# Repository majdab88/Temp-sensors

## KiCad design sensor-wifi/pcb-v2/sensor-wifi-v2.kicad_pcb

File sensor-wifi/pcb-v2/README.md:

# sensor-wifi PCB v2 — TP4056 module instead of the on-board charger

Same board as v1 (`../pcb`), with the USB-C receptacle, the BQ24074 charger and
the DW01A/8205A cell protection replaced by a **TP4056 Mini Type-C charger
module** (14 × 17.5 mm, with its own protection) soldered flat onto the PCB.
The point is cost: JLCPCB's Extended parts drop from 11 to **4**. The v1 design
is kept unchanged in `../pcb`.

**Status:** placed and routed. ERC clean; DRC 0 errors, 0 unconnected,
schematic parity clean. The 45 warnings are silkscreen overlaps. Not built.

## What changed from v1

| | v1 | v2 |
|---|---|---|
| USB input | J1 USB-C, F1 PTC, D1 TVS, CC and shield parts | the module's own USB-C (J1's place, same enclosure wall) |
| Charging | BQ24074, 0.5 A, power path, TS thermistor | module's TP4056 (4056H), **~0.6 A** (its R_PROG is 2 kΩ) |
| Cell protection | DW01A + 8205A + F2 3 A fuse | module's single-chip protector |
| Reverse cell | Q1 (P-FET, + side), DW01A fed through D2 | **Q1 + Q2** (N-FET, − side), see below |
| USB present | BQ24074 `/PGOOD` → GPIO7, active **low** | **100 k / 100 k from module IN+ → GPIO7, active high** |
| Charging status | `/CHG` → GPIO18 | none (GPIO18 unused) |
| Everything else | | unchanged and at v1's positions: module, TPS63802 loop, NTC, buttons, J_PROG, crystal, holder |

**Firmware:** `USB_DET` (GPIO7) is HIGH when USB is present, the opposite of
`/PGOOD`; GPIO7 is still an LP GPIO, so it still wakes from deep sleep. Drop the
`/CHG` reading. The battery divider (GPIO2/GPIO21) is unchanged and now sits on
VSYS, which is the cell through Q1 (≈ 4.2 V while USB charges).

## The module

`TP4056_Mini_TypeC` footprint and symbol come from `routing/mkfp_tp4056.py`,
measured from the vendor STEP (`3d/TP4056_Mini.step`, GrabCAD, **not committed**:
its licence does not allow redistribution). Six plated holes, 1.0 mm:

| Pad | Name | Net | Position on the board |
|---|---|---|---|
| 1 | IN+ | `VBUS_IN` (divider only) | 101.85, 186.5 |
| 2 | IN− | GND | 114.15, 186.5 |
| 3 | OUT− | GND | 114.15, 172.5 |
| 4 | B− | `BATN` (Q2 source) | 111.61, 172.5 |
| 5 | (unlabelled) | **isolated**, mechanical only | 104.39, 172.5 |
| 6 | + | `VSYS` | 101.85, 172.5 |

- **Solder it** with cut-down pin-header pins through both boards, or let solder
  fill its holes onto our pads. The 18650 holder is on the back but clear of
  the module, so the joints are reachable from below.
- **Pad 5 is not connected** until a continuity check confirms it is a second
  "+" (it probably is). Beep pad 5 to pad 6 on a real module.
- **Check IN− to OUT− continuity**: the USB-detect divider assumes they are the
  same node (they are on standard TP4056 boards).
- **CC resistors**: look for two 5.1 kΩ (512) resistors by the module's USB-C.
  Without them it charges only from USB-A-to-C cables, not C-to-C.
- **No power path**: the ESP draws from the cell node the TP4056 charges. Once the
  cell is full it terminates, the load draws it down to ~4.05 V, and it tops up:
  shallow cycles near full, accepted for this load.
- **No cold-charge cutoff**: the module grounds the TP4056's TEMP pin.
- **Enclosure**: the module's receptacle face is where J1's was (board edge
  + 1.05 mm), but its centre is ~2.6 mm above our board (it sits on the module's
  own PCB), about 1 mm higher than J1's. Move the enclosure's USB opening up to
  match before printing.

## Reverse-cell protection (Q1 + Q2)

With the module, a P-FET on the + side alone (v1's Q1) is not enough. The module's
protector sits between B− and ground and is powered from the charger, so with a
reversed cell **and** USB present Q1 would turn on and the charger would drive
current through the reversed cell. v2 adds an N-FET on the − side:

- **Q1** (AO3401A, P): drain = holder +, source = VSYS, gate via R10 (10 k) to
  holder −, R11 (1 M) to source.
- **Q2** (AO3400A, N, Basic C20917): drain = holder −, source = module B−
  (`BATN`), gate via R12 (10 k) to holder +, R13 (1 M) to source.

| Cell | USB | Q1 | Q2 | Result |
|---|---|---|---|---|
| correct | no / yes | on | on | normal; charge and discharge both ways through both |
| reversed | no | off | off | no path |
| reversed | yes | off | off | each would need the other already on to turn on; no current |

The reversed rows are reasoned, not measured. **Bench-test them** (reversed cell
on a current-limited supply, with and without USB: zero current, no heating)
before trusting the board. This is a safety path.

## JLCPCB parts

21 part numbers: **15 Basic, 2 Preferred, 4 Extended** (U1 ESP32-C6-MINI-1U-H4,
U4 TPS63802, L1 inductor, F3 probe-line PTC). Every SMD part carries `LCSC`, `MPN`
and `Manufacturer`. Hand-soldered: the TP4056 module, BT1 holder (back side),
J2, J3, SW1, SW2.

## Layout

- v1's outline (64 × 90 mm), M3 holes and every kept part at v1's coordinates.
- **Module** where J1 was: centre (108, 180.4), rotated 180°, USB-C out of the
  bottom edge.
- **Q2, R12, R13** beside the holder's − contact (top right), where the DW01A and
  8205A were. **C4/C5** (10 µF) beside the module's + pad. **R8/R9** (USB detect)
  left of the module.
- **Hand-routed** (`routing/handroutes.py`): v1's TPS63802 loop, UART lanes and
  GND ties unchanged; the cell paths (holder + → Q1; holder − → Q2 on 0.8 mm;
  Q2 → module B− on 1 mm down the back); the VSYS trunk from the module's + pad to
  the regulator, Q1 and the battery divider (v1's pinned path for the last part);
  all of EN (Freerouting left a link open); and a back-side tie for C16's ground
  via. Freerouting routed the rest.
- The holder's three plastic pegs go through the board at (131, 172.6),
  (147, 117.4) and (147, 181.1); the VSYS trunk passes the first with 0.8 mm.

## Reproducing it

Same tooling as sensor-ntc v3. Under KiCad's bundled Python:

1. `routing/mkfp_tp4056.py` (any Python) writes the module footprint and symbol.
2. `routing/mkboard.py` builds the unrouted board from the schematic's netlist
   and the placement table.
3. `routing/build.py auto` hand-routes, autoroutes, pours, stitches and runs
   DRC on a copy in `routing/work/`. Good when it reports 0 unconnected; adopt by
   copying `routing/work/sensor-wifi-v2.kicad_pcb` over the project file with
   KiCad closed. `routing/drc-baseline.json` is the adopted board's DRC.

## Before fab

- Continuity checks on a real module: pad 5 ↔ pad 6, IN− ↔ OUT−; CC resistors.
- Move the enclosure's USB opening up ~1 mm for the module's receptacle.
- Tidy the silkscreen; mark pin 1 on J_PROG.
- Bench-test the reverse-cell rows after assembly.

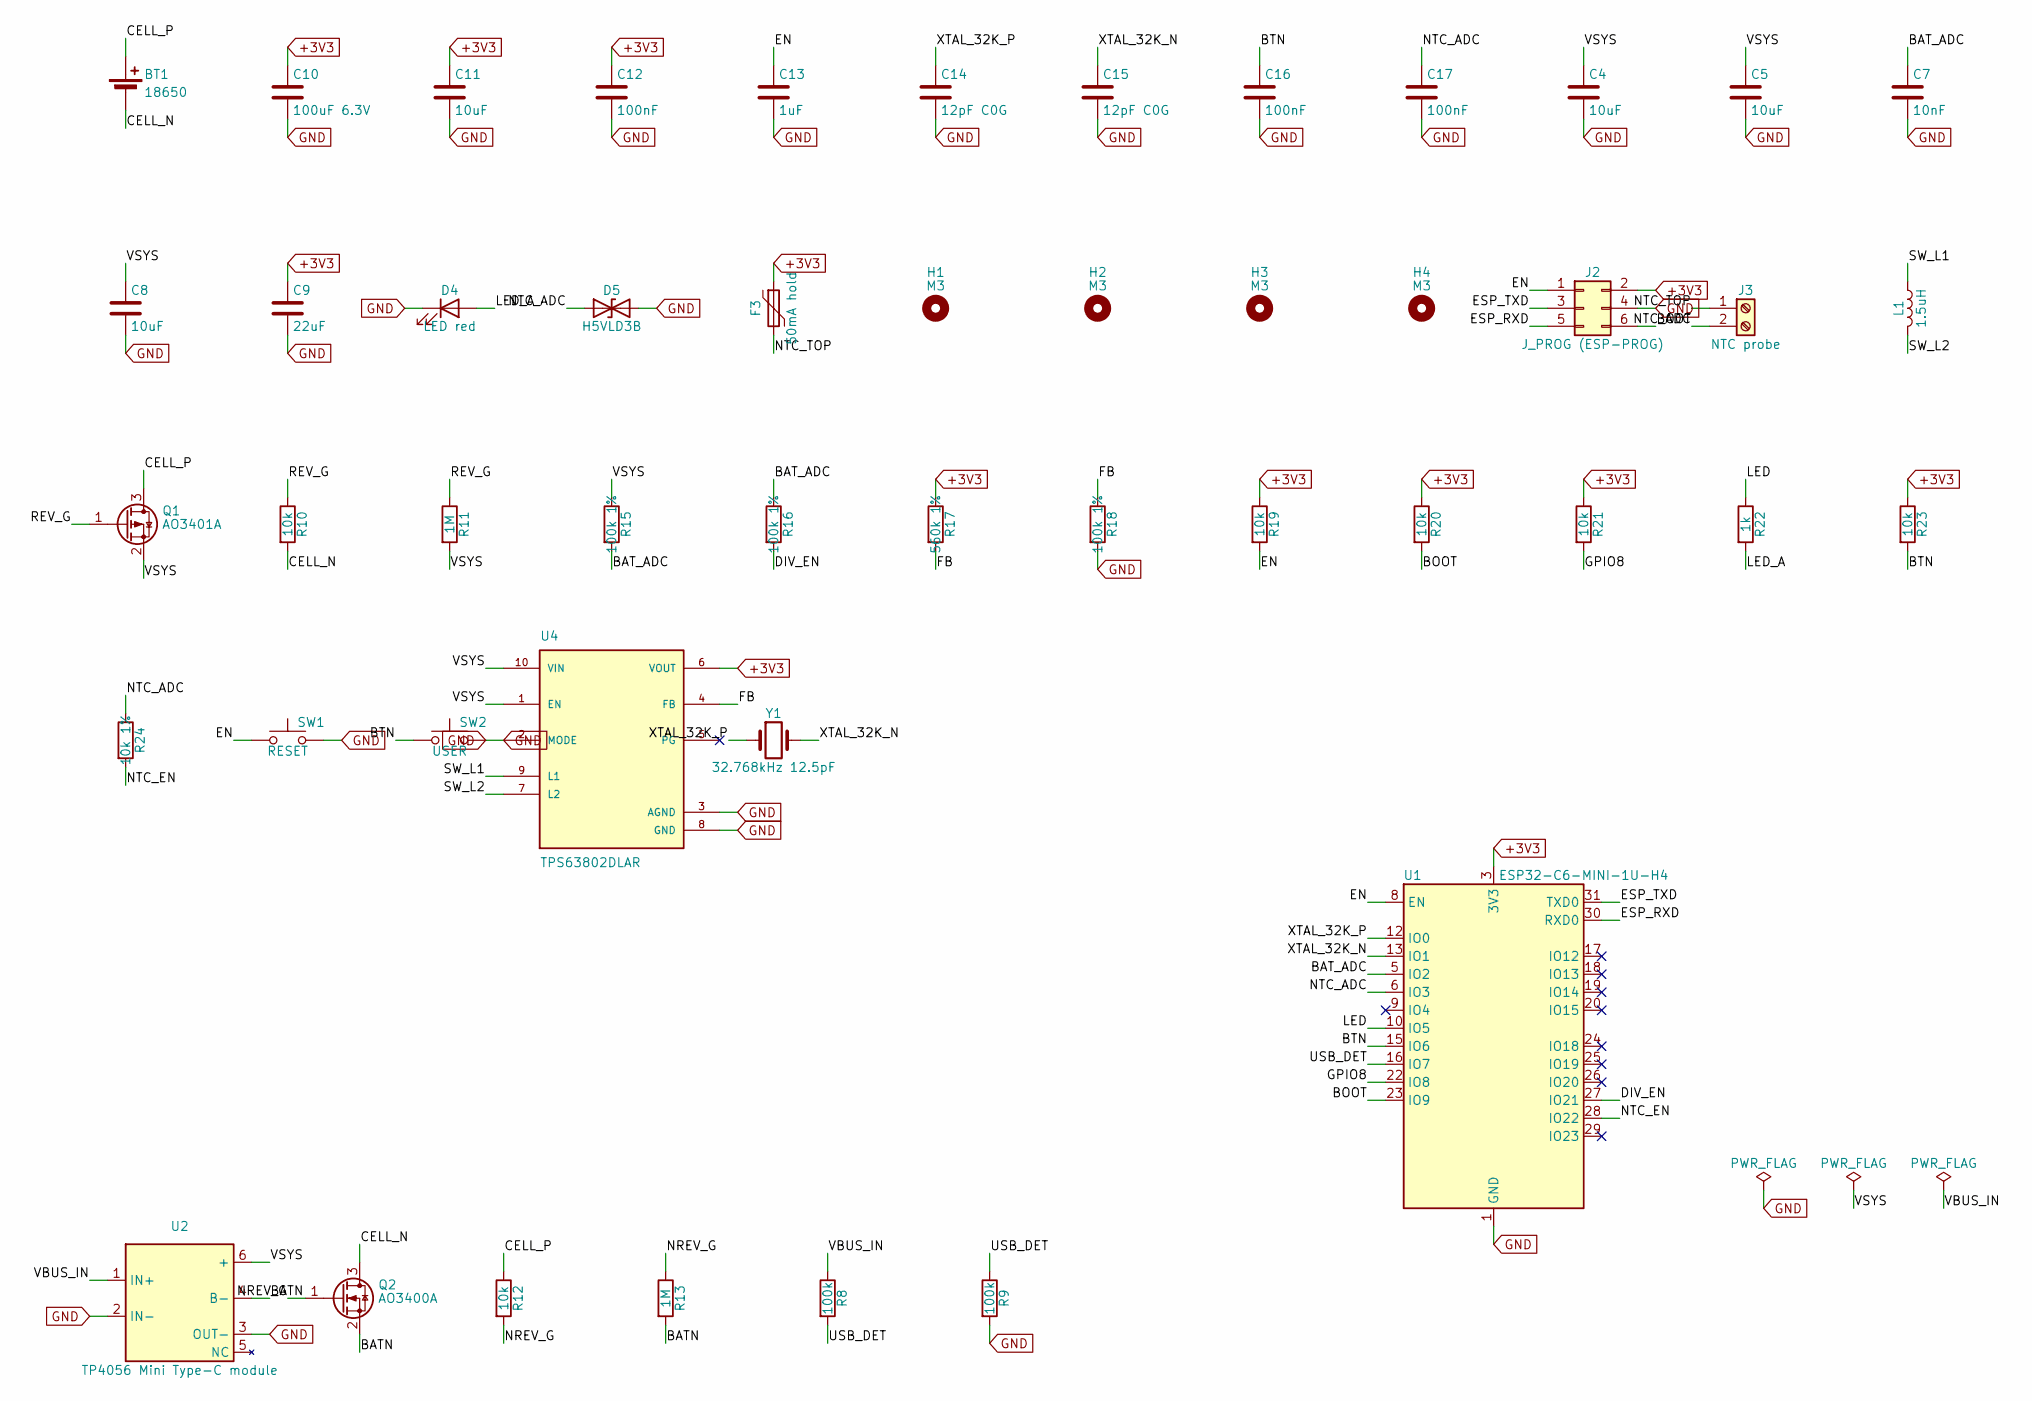
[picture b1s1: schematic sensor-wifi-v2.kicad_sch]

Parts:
BT1: 18650; BatteryHolder_Keystone_1042_1x18650
C4, C5, C8, C11: 10uF; C_0805_2012Metric; MPN CL21A106KAYNNNE; LCSC C15850
C7: 10nF; C_0603_1608Metric; MPN 0603B103K500NT; LCSC C57112
C9: 22uF; C_1206_3216Metric; MPN CL31A226KAHNNNE; LCSC C12891
C10: 100uF 6.3V; C_1206_3216Metric; MPN CL31A107MQHNNNE; LCSC C15008
C12, C16, C17: 100nF; C_0603_1608Metric; MPN CC0603KRX7R9BB104; LCSC C14663
C13: 1uF; C_0603_1608Metric; MPN CL10A105KB8NNNC; LCSC C15849
C14, C15: 12pF C0G; C_0603_1608Metric; MPN CL10C120JB8NNNC; LCSC C38523
D4: LED red; LED_0603_1608Metric; MPN KT-0603R; LCSC C2286
D5: H5VLD3B; D_SOD-323; MPN H5VLD3B; LCSC C20615805
F3: 50mA hold; Fuse_0805_2012Metric; MPN BSMD0805-005-60V; LCSC C960019
H1, H2, H3, H4: M3; MountingHole_3.2mm_M3
J2: J_PROG (ESP-PROG); IDC-Header_2x03_P2.54mm_Vertical
J3: NTC probe; TerminalBlock_Phoenix_PT-1,5-2-3.5-H_1x02_P3.50mm_Horizontal
L1: 1.5uH; VLS3015; MPN FNR3015S1R5MT; LCSC C167745
Q1: AO3401A; SOT-23; MPN AO3401A; LCSC C15127
Q2: AO3400A; SOT-23; MPN AO3400A; LCSC C20917
R8, R9: 100k; R_0603_1608Metric; MPN 0603WAF1003T5E; LCSC C25803
R10, R12, R19, R20, R21, R23: 10k; R_0603_1608Metric; MPN 0603WAF1002T5E; LCSC C25804
R11, R13: 1M; R_0603_1608Metric; MPN 0603WAF1004T5E; LCSC C22935
R15, R16, R18: 100k 1%; R_0603_1608Metric; MPN 0603WAF1003T5E; LCSC C25803
R17: 560k 1%; R_0603_1608Metric; MPN 0603WAF5603T5E; LCSC C23203
R22: 1k; R_0603_1608Metric; MPN 0603WAF1001T5E; LCSC C21190
R24: 10k 1%; R_0603_1608Metric; MPN 0603WAF1002T5E; LCSC C25804
SW1: RESET; SW_PUSH_6mm_H5mm
SW2: USER; SW_PUSH_6mm_H5mm
U1: ESP32-C6-MINI-1U-H4; ESP32-C6-MINI-1U; MPN ESP32-C6-MINI-1U-H4; LCSC C20627095
U2: TP4056 Mini Type-C module; TP4056_Mini_TypeC
U4: TPS63802DLAR; VREG_TPS63802DLAR; PARTREV B; LCSC C2845237
Y1: 32.768kHz 12.5pF; Crystal_SMD_3215-2Pin_3.2x1.5mm; MPN Q13FC13500004; LCSC C32346

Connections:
+3V3: C9.1, C10.1, C11.1, C12.1, F3.1, J2.2, R17.1, R19.1, R20.1, R21.1, R23.1, U1.3 (3V3), U4.6 (VOUT)
/BATN: Q2.2 (S), R13.2, U2.4 (B-)
/BAT_ADC: C7.1, R15.2, R16.1, U1.5 (IO2)
/BOOT: J2.6, R20.2, U1.23 (IO9)
/BTN: C16.1, R23.2, SW2.1, U1.15 (IO6)
/CELL_N: BT1.2 (-), Q2.3 (D), R10.2
/CELL_P: BT1.1 (+), Q1.3 (D), R12.1
/DIV_EN: R16.2, U1.27 (IO21)
/EN: C13.1, J2.1, R19.2, SW1.1, U1.8 (EN)
/ESP_RXD: J2.5, U1.30 (RXD0)
/ESP_TXD: J2.3, U1.31 (TXD0)
/FB: R17.2, R18.1, U4.4 (FB)
/GPIO8: R21.2, U1.22 (IO8)
/LED: R22.1, U1.10 (IO5)
/LED_A: D4.2 (A), R22.2
/NREV_G: Q2.1 (G), R12.2, R13.1
/NTC_ADC: C17.1, D5.1 (A1), J3.2, R24.1, U1.6 (IO3)
/NTC_EN: R24.2, U1.28 (IO22)
/NTC_TOP: F3.2, J3.1
/REV_G: Q1.1 (G), R10.1, R11.1
/SW_L1: L1.1, U4.9 (L1)
/SW_L2: L1.2, U4.7 (L2)
/USB_DET: R8.2, R9.1, U1.16 (IO7)
/VBUS_IN: R8.1, U2.1 (IN+)
/VSYS: C4.1, C5.1, C8.1, Q1.2 (S), R11.2, R15.1, U2.6 (+), U4.1 (EN), U4.10 (VIN)
/XTAL_32K_N: C15.1, U1.13 (IO1), Y1.2
/XTAL_32K_P: C14.1, U1.12 (IO0), Y1.1
GND: C4.2, C5.2, C7.2, C8.2, C9.2, C10.2, C11.2, C12.2, C13.2, C14.2, C15.2, C16.2, C17.2, D4.1 (K), D5.2 (A2), J2.4, R9.2, R18.2, SW1.2, SW2.2, U1.1 (GND), U1.2 (GND), U1.11 (GND), U1.14 (GND), U1.36 (GND), U1.37 (GND), U1.38 (GND), U1.39 (GND), U1.40 (GND), U1.41 (GND), U1.42 (GND), U1.43 (GND), U1.44 (GND), U1.45 (GND), U1.46 (GND), U1.47 (GND), U1.48 (GND), U1.49 (GND), U1.50 (GND), U1.51 (GND), U1.52 (GND), U1.53 (GND), U2.2 (IN-), U2.3 (OUT-), U4.2 (MODE), U4.3 (AGND), U4.8 (GND)

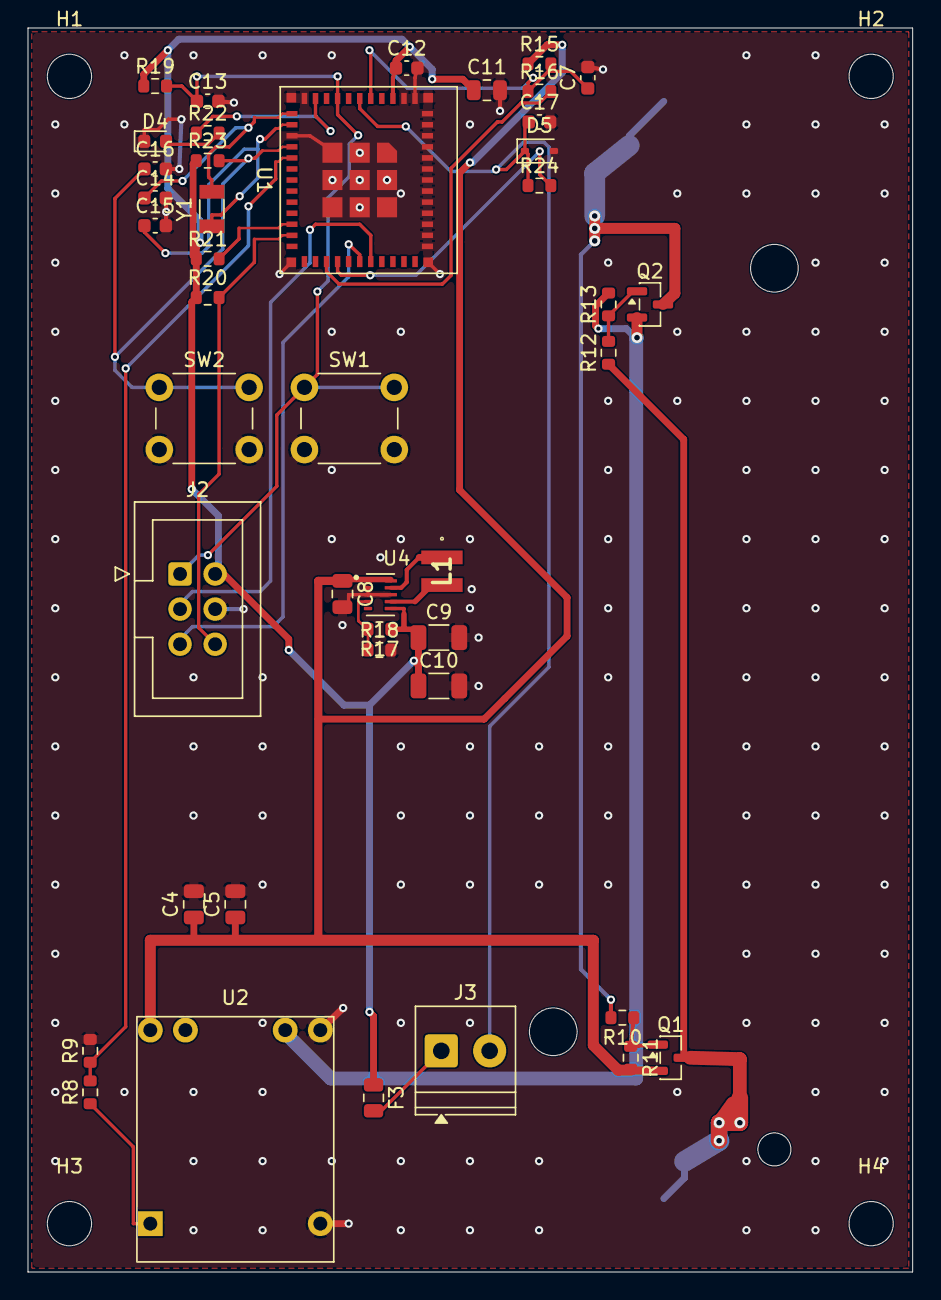
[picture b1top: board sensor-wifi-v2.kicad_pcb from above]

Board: 2 copper layers, 64.0 x 90.0 mm, 48 parts (1 on the bottom side), 28 nets.

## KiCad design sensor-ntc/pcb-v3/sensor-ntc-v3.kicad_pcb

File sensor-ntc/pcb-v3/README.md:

# sensor-ntc v3 PCB

The v2 sensor board, redesigned around the **ESP32-C6-MINI-1U-H4** (the module
sensor-wifi uses), with the NTC back on the **high side** and a connector for the
**12 mm panel button with its LED ring**. KiCad 10 project, 2 layers, 1.6 mm.

Placed and routed. **DRC: 0 errors, 0 unconnected, schematic parity clean.** The
59 remaining findings are silkscreen text overlaps (a GUI tidy job) and two
reference labels near the board edge. Not yet fabricated.

## What changed from v2

| | v2 (NTC_SENSOR) | v3 |
|---|---|---|
| Module | ESP32-C6-WROOM-1U-N4 (not stocked at JLCPCB) | **ESP32-C6-MINI-1U-H4** (C20627095), −40…105 °C, u.FL |
| NTC | low side: `3V3 → R5 → ADC → NTC → GPIO22` | **high side**: `3V3 → NTC → ADC → R5 → GPIO22` |
| Panel button | none | `J_BTN` 4-pin JST XH + BSS138 low-side LED driver on GPIO23 |
| Passives | no LCSC numbers | every SMD part carries an `LCSC` field; all Basic/Preferred |
| Inductor | TDK VLS3015CX-1R5M-H (not stocked) | cjiang FNR3015S1R5MT (C167745), same 3×3 land |
| 22 µF | 1210 (Extended) | 1206 (C12891, Basic), same pad pitch |
| Outline, holes, power section | | **unchanged**: same 60 × 40 mm, same four holes, same TPS63802 placement and copper |

The outline and mounting holes are v2's, so the board drops into the existing
top-lid enclosure (`../enclosure/sensor-ntc-v2-toplid.sc`).

## Pin map

The same GPIOs as v2, so the firmware only needs the high-side formula and the
panel LED. The MINI does not bring out IO10/IO11; nothing used them.

| GPIO | MINI pin | Net | Function |
|---|---|---|---|
| 0 | 12 | `D0_BTN` | On-board SW2, panel button (`J_BTN` pin 3). 10 k pull-up, 100 nF. LP GPIO, deep-sleep wake |
| 1 | 13 | `NTC_ADC` | NTC divider midpoint, 100 nF to GND |
| 2 | 5 | `BAT_ADC` | Battery divider midpoint (100 k / 100 k), 10 nF |
| 5 | 10 | `LED` | On-board red LED via 1 k (bench indicator) |
| 8 | 22 | `GPIO8` | Strap: 10 k pull-up |
| 9 | 23 | `BOOT` | Strap: 10 k pull-up; `J_PROG` pin 6 |
| 21 | 27 | `DIV_EN` | Battery divider enable (LOW = on, Hi-Z in sleep) |
| 22 | 28 | `NTC_EN` | NTC divider enable (LOW = on, Hi-Z in sleep) |
| 23 | 29 | `PANEL_LED_G` | Panel LED: BSS138 gate, 100 k pull-down |
| 16 / 17 | 31 / 30 | `ESP_TXD` / `ESP_RXD` | `J_PROG` pins 3 / 5 |
| EN | 8 | `EN` | 10 k pull-up, 1 µF, SW1 RESET, `J_PROG` pin 1 |
| 3, 4, 6, 7, 12–15, 18–20 | | | unconnected (15 floats high: boot log on) |

**NTC formula on v3:** `R_ntc = r_series · (Vcc − V) / V`. That is the v1 form,
not v2's. A cold probe has a high resistance, which keeps the ADC low, where it is
accurate: −18 °C (81.9 kΩ) reads 0.36 V and +4 °C (26.8 kΩ) 0.90 V. One probe
wire carries 3V3 continuously. That is harmless on a floating battery board; it
mattered on sensor-wifi, which can be earthed through USB.

## Connectors (all hand-soldered, like v2)

| Ref | Part | Pins |
|---|---|---|
| `BT1` | JST XH 2-pin | 1 `V_BAT`, 2 GND (as v2) |
| `TH1` | JST XH 2-pin | 1 3V3, 2 `NTC_ADC` (probe is not polarised) |
| `J_BTN` | JST XH 4-pin | 1 LED+ (3V3), 2 LED− (to the FET via `R_bled1`), 3 SW (`D0_BTN`), 4 GND |
| `J_PROG` | 2×3 IDC, ESP-PROG UART | 1 EN, 2 3V3, 3 TXD, 4 GND, 5 RXD, 6 IO0 (= GPIO9) |
| `SW1` / `SW2` | 6 mm THT tactile | RESET / D0 |
| `C1` | 1000 µF 6.3 V radial Ø8 | cell-side bulk, as v2 |

**Panel LED.** The 12 mm button's ring has its own series resistor (that is what
"3–8 V" on such buttons means). `R_bled1` (0 Ω) is the only brightness trim:
fit a resistor there to dim it. The FET's 100 k gate pull-down keeps the LED
off through reset, deep sleep and brown-out. Use a red or yellow ring: blue,
white and green have Vf 3.0–3.2 V and barely light from 3.3 V.

## JLCPCB parts

Every SMD part is from JLCPCB's catalogue, Basic or Preferred where one exists.
The three **Extended** parts have no Basic equivalent at all: JLCPCB's Basic
library has no RF module, no buck-boost, no power inductor at this rating, and no
connectors. Stock figures are from the catalogue snapshot of 2026-11-25.

| Refs | Value | LCSC | Part | Library | Stock |
|---|---|---|---|---|---|
| U1 | ESP32-C6-MINI-1U-H4 | C20627095 | Espressif | **Extended** | 3 500 |
| U2 | TPS63802DLAR | C2845237 | TI | **Extended** | 14 934 |
| L1 | 1.5 µH, 2.7 A sat, 65 mΩ | C167745 | cjiang FNR3015S1R5MT | **Extended** | 5 340 |
| C_buf1, C_out1 | 22 µF 25 V X5R 1206 | C12891 | Samsung CL31A226KAHNNNE | Basic | |
| C_in1, C_vdd_bulk1 | 10 µF 25 V X5R 0805 | C15850 | Samsung CL21A106KAYNNNE | Basic | |
| C_en1 | 1 µF X7R 0805 | C28323 | Samsung | Basic | |
| C_d0, C_vdd_hf1, Cfn1 | 100 nF X7R 0805 | C49678 | Yageo | Basic | |
| Cfb1 | 10 nF X7R 0805 | C1710 | Samsung | Basic | |
| R1 | 560 k 1 % 0603 | C23203 | Uniroyal | Preferred | |
| R2, R3, R4, R_gpd1 | 100 k 1 % 0603 | C25803 | Uniroyal | Basic | |
| R5, R_boot1, R_en1, R_gpio0, R_gpio8 | 10 k 1 % 0603 | C25804 | Uniroyal | Basic | |
| R_LED1 | 1 k 0603 | C21190 | Uniroyal | Basic | |
| R_bled1 | 0 Ω 0603 | C21189 | Uniroyal | Basic | |
| D1 | red LED 0603 | C2286 | KENTO KT-0603R | Basic | |
| Q1 | BSS138 SOT-23 | C7420339 | hongjiacheng | Preferred | |

X5R is rated to −55 °C, so the Basic X5R 10 µF and 22 µF parts are fine in a
freezer. **Check before ordering:** the FNR3015's recommended land pattern
against the `VLS3015` footprint (both are two-terminal 3 × 3 mm; the pads are
1 × 3 mm at ±1 mm), and that stock still covers the build.

The JLCPCB BOM and placement file can come from the Fabrication Toolkit plugin
(as v2's order did); it reads the `LCSC` field, which is on every footprint.

## Layout

- **Power section** (bottom left): v2's parts at v2's positions, with v2's
  copper copied segment for segment (`routing/handroutes.py`). That loop is
  the part of the board that decides whether a node survives a TX burst on cold
  cells.
- **Module** in the middle, u.FL toward the top edge. Decoupling and the EN RC on
  its left, straps and the D0/NTC filter caps under it.
- **`J_BTN` on the top edge**, which faces the +X end wall and the panel button.
- **`TH1` on the right**, near the probe hole in the −Y wall. The probe's inside
  M6 nut sweeps `x ≥ 109.5, y 90…101.5` just above the copper (enclosure
  coordinates: probe axis `ex 17.8`). Nothing tall sits there, and TH1 starts
  below it.
- **Copper.** Signals are 0.25 mm. `Power` (V_BAT, 3V3) is 0.5 mm. Minimum track
  width is 0.15 mm. GND pours on both layers, about 50 stitching vias.
- **Hand-routed and locked** (Freerouting's result differs between runs and
  dropped one branch or another): the TPS63802 cluster, **all of 3V3** (trunk
  from the regulator down B.Cu between SW2 and SW1, under the module's bottom
  edge, up to U1 pin 3 and its caps, with branches to the pull-ups, TH1,
  J_PROG, R_en1 and J_BTN), the module's centre GND array (vias in pad), and
  ground ties for pads that tracks fence off from the pour (U1 pads 11, 14, 50,
  51, C_en1, C_d0, Cfn1, D1, R2).
- **`sensor-ntc-v3.kicad_dru`** has one exception: J_BTN's GND pin gets one
  back-side thermal spoke. The front pour reaches it fully.
- **The B.Cu pour has three voids** (left of the module around J_PROG, and above
  SW2), fenced off by tracks and removed as islands. Every GND pad is still
  connected (DRC: 0 unconnected); it is ground-plane area lost, not a fault.

## Reproducing it

All of it runs under KiCad's bundled Python (`C:\Program Files\KiCad\10.0\bin\python.exe`).

1. **Schematic** (`sensor-ntc-v3.kicad_sch`) is the source of truth. It was
   authored with Copperpour and is ERC-clean.
2. **`routing/mkboard.py`** builds the *unrouted* board from the schematic's
   netlist: outline, footprints, fields, nets, and the placement table. It
   overwrites `sensor-ntc-v3.kicad_pcb`, so edit placement there, not in the PCB
   editor, until the layout is frozen.
3. **`routing/build.py auto`** copies the board to `routing/work/`, strips any
   copper, adds `handroutes.py`, pours, autoroutes (DSN → Freerouting 2.4.1 →
   SES), stitches, and runs DRC with schematic parity. About 2 minutes. A run is
   good when it reports 0 unconnected. Adopt it by copying
   `routing/work/sensor-ntc-v3.kicad_pcb` over the project file with KiCad closed.
4. `routing/drc-baseline.json` is the DRC of the adopted board. Compare against
   it, not against zero, after any change.

## Before fab

- Tidy the silkscreen (reference text overlaps), mark pin 1 on `J_PROG`.
- Check the u.FL plug and its cable clear `J_BTN` (the plug sits about 2.5 mm
  from the connector body; the cable exits sideways).
- **Clash-check against the enclosure**: export the STEP
  (`kicad-cli pcb export step --subst-models --include-tracks`) and replace the
  `PCB` import in the SolidCraft model. TH1 and J_BTN are new positions. Also check
  the M2 screw head at H2 against the probe nut's corners (inherited from v2,
  about 1 mm apart).
- Firmware: a `BOARD_REV 3` with v2's pins, the high-side NTC formula, and the
  panel LED on GPIO23.
- 3D models: `L1` and `U2` still point at absolute paths on the dev machine, as
  in v2 and sensor-wifi. `U1`'s is in `3d/`.

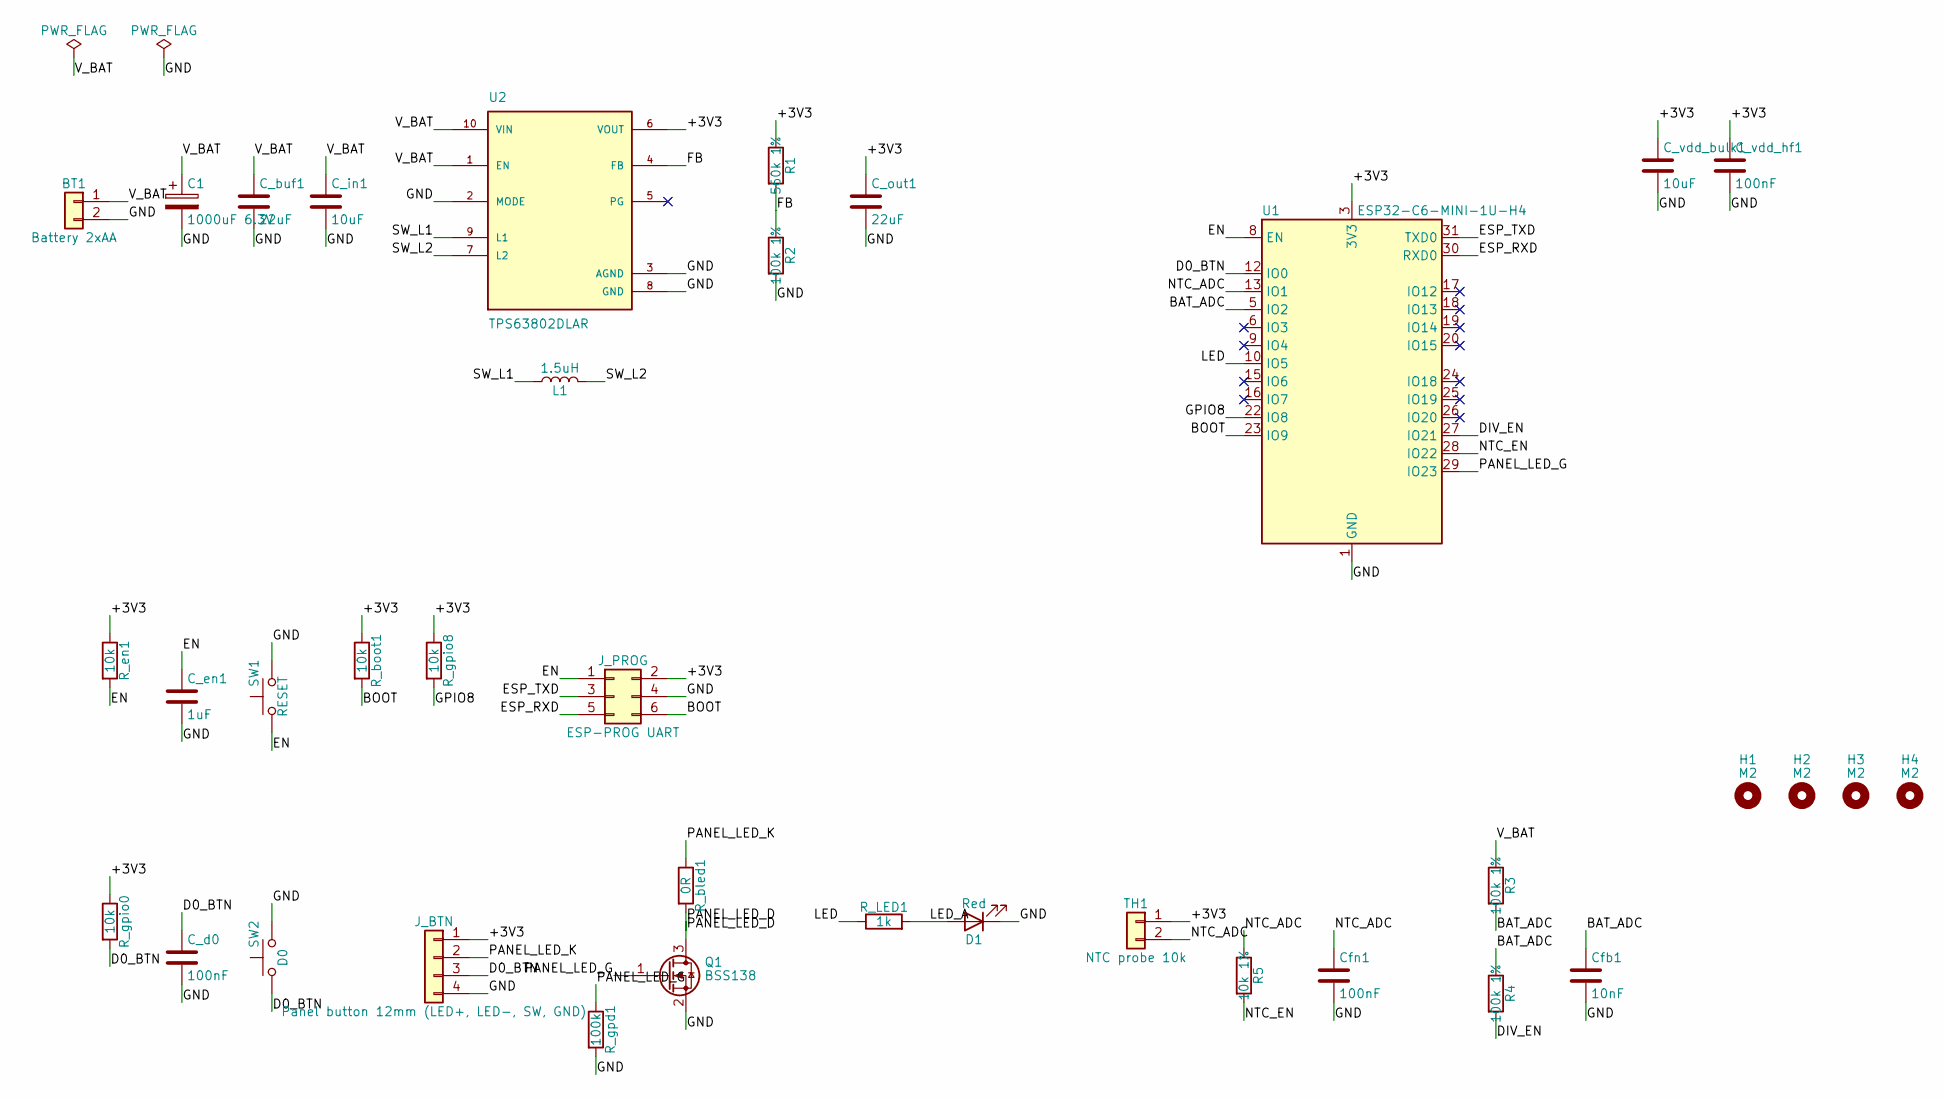
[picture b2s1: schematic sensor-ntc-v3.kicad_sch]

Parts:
BT1: Battery 2xAA; JST_XH_B2B-XH-A_1x02_P2.50mm_Vertical
C1: 1000uF 6.3V; CP_Radial_D8.0mm_P3.50mm
C_buf1: 22uF; C_1206_3216Metric; MPN CL31A226KAHNNNE; LCSC C12891
C_d0: 100nF; C_0805_2012Metric; MPN CC0805KRX7R9BB104; LCSC C49678
C_en1: 1uF; C_0805_2012Metric; MPN CL21B105KBFNNNE; LCSC C28323
C_in1: 10uF; C_0805_2012Metric; MPN CL21A106KAYNNNE; LCSC C15850
C_out1: 22uF; C_1206_3216Metric; MPN CL31A226KAHNNNE; LCSC C12891
C_vdd_bulk1: 10uF; C_0805_2012Metric; MPN CL21A106KAYNNNE; LCSC C15850
C_vdd_hf1: 100nF; C_0805_2012Metric; MPN CC0805KRX7R9BB104; LCSC C49678
Cfb1: 10nF; C_0805_2012Metric; MPN CL21B103KBANNNC; LCSC C1710
Cfn1: 100nF; C_0805_2012Metric; MPN CC0805KRX7R9BB104; LCSC C49678
D1: Red; LED_0603_1608Metric; MPN KT-0603R; LCSC C2286
H1, H2, H3, H4: M2; MountingHole_2.5mm
J_BTN: Panel button 12mm (LED+, LED-, SW, GND); JST_XH_B4B-XH-A_1x04_P2.50mm_Vertical
J_PROG: ESP-PROG UART; IDC-Header_2x03_P2.54mm_Vertical
L1: 1.5uH; VLS3015; MPN FNR3015S1R5MT; LCSC C167745
Q1: BSS138; SOT-23; MPN BSS138; LCSC C7420339
R1: 560k 1%; R_0603_1608Metric; MPN 0603WAF5603T5E; LCSC C23203
R2, R3, R4: 100k 1%; R_0603_1608Metric; MPN 0603WAF1003T5E; LCSC C25803
R5: 10k 1%; R_0603_1608Metric; MPN 0603WAF1002T5E; LCSC C25804
R_LED1: 1k; R_0603_1608Metric; MPN 0603WAF1001T5E; LCSC C21190
R_bled1: 0R; R_0603_1608Metric; MPN 0603WAF0000T5E; LCSC C21189
R_boot1: 10k; R_0603_1608Metric; MPN 0603WAF1002T5E; LCSC C25804
R_en1: 10k; R_0603_1608Metric; MPN 0603WAF1002T5E; LCSC C25804
R_gpd1: 100k; R_0603_1608Metric; MPN 0603WAF1003T5E; LCSC C25803
R_gpio0, R_gpio8: 10k; R_0603_1608Metric; MPN 0603WAF1002T5E; LCSC C25804
SW1: RESET; SW_PUSH_6mm_H5mm
SW2: D0; SW_PUSH_6mm_H5mm
TH1: NTC probe 10k; JST_XH_B2B-XH-A_1x02_P2.50mm_Vertical
U1: ESP32-C6-MINI-1U-H4; ESP32-C6-MINI-1U; MPN ESP32-C6-MINI-1U-H4; LCSC C20627095
U2: TPS63802DLAR; VREG_TPS63802DLAR; PARTREV B; LCSC C2845237

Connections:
/+3V3: C_out1.1, C_vdd_bulk1.1, C_vdd_hf1.1, J_BTN.1, J_PROG.2, R1.1, R_boot1.1, R_en1.1, R_gpio0.1, R_gpio8.1, TH1.1, U1.3 (3V3), U2.6 (VOUT)
/BAT_ADC: Cfb1.1, R3.2, R4.1, U1.5 (IO2)
/BOOT: J_PROG.6, R_boot1.2, U1.23 (IO9)
/D0_BTN: C_d0.1, J_BTN.3, R_gpio0.2, SW2.1, U1.12 (IO0)
/DIV_EN: R4.2, U1.27 (IO21)
/EN: C_en1.1, J_PROG.1, R_en1.2, SW1.1, U1.8 (EN)
/ESP_RXD: J_PROG.5, U1.30 (RXD0)
/ESP_TXD: J_PROG.3, U1.31 (TXD0)
/FB: R1.2, R2.1, U2.4 (FB)
/GND: BT1.2, C1.2, C_buf1.2, C_d0.2, C_en1.2, C_in1.2, C_out1.2, C_vdd_bulk1.2, C_vdd_hf1.2, Cfb1.2, Cfn1.2, D1.1 (K), J_BTN.4, J_PROG.4, Q1.2 (S), R2.2, R_gpd1.2, SW1.2, SW2.2, U1.1 (GND), U1.2 (GND), U1.11 (GND), U1.14 (GND), U1.36 (GND), U1.37 (GND), U1.38 (GND), U1.39 (GND), U1.40 (GND), U1.41 (GND), U1.42 (GND), U1.43 (GND), U1.44 (GND), U1.45 (GND), U1.46 (GND), U1.47 (GND), U1.48 (GND), U1.49 (GND), U1.50 (GND), U1.51 (GND), U1.52 (GND), U1.53 (GND), U2.2 (MODE), U2.3 (AGND), U2.8 (GND)
/GPIO8: R_gpio8.2, U1.22 (IO8)
/LED: R_LED1.1, U1.10 (IO5)
/LED_A: D1.2 (A), R_LED1.2
/NTC_ADC: Cfn1.1, R5.1, TH1.2, U1.13 (IO1)
/NTC_EN: R5.2, U1.28 (IO22)
/PANEL_LED_D: Q1.3 (D), R_bled1.2
/PANEL_LED_G: Q1.1 (G), R_gpd1.1, U1.29 (IO23)
/PANEL_LED_K: J_BTN.2, R_bled1.1
/SW_L1: L1.1, U2.9 (L1)
/SW_L2: L1.2, U2.7 (L2)
/V_BAT: BT1.1, C1.1, C_buf1.1, C_in1.1, R3.1, U2.1 (EN), U2.10 (VIN)

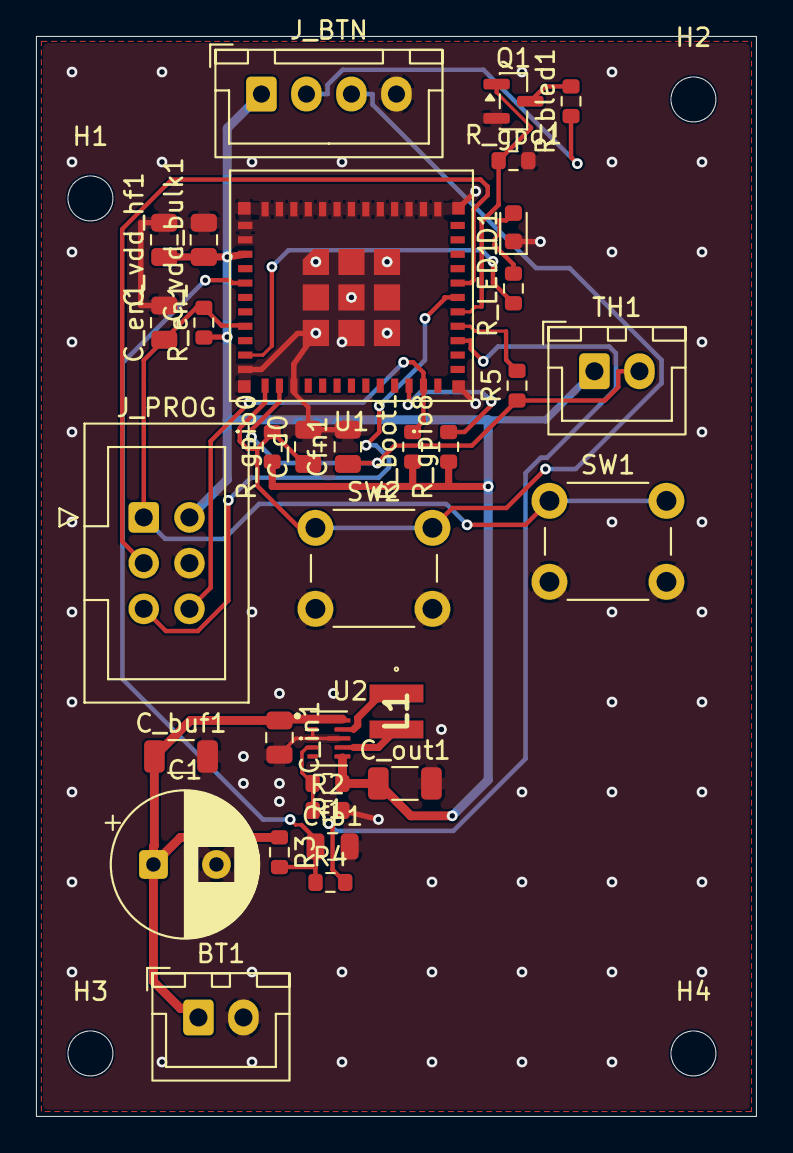
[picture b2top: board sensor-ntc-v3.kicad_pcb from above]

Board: 2 copper layers, 40.0 x 60.0 mm, 37 parts (0 on the bottom side), 21 nets.

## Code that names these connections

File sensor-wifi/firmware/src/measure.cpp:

#include "measure.h"
#include "config.h"
#include "settings.h"

void measureInitPins() {
  // Both dividers are switched on their low side; Hi-Z means no current.
  pinMode(NTC_EN_PIN, INPUT);
  pinMode(BAT_DIV_EN_PIN, INPUT);
  // /PGOOD and /CHG are open drain with external 100k pull-ups.
  pinMode(PGOOD_PIN, INPUT);
  pinMode(CHG_PIN, INPUT);
  pinMode(BUTTON_PIN, INPUT_PULLUP);
  analogReadResolution(12);
}

bool mainsPresent() { return digitalRead(PGOOD_PIN) == LOW; }
bool isCharging()   { return digitalRead(CHG_PIN) == LOW; }

static float averageMv(int pin, int samples) {
  analogReadMilliVolts(pin);      // discard the first conversion
  delay(5);
  long sum = 0;
  for (int i = 0; i < samples; i++) {
    sum += analogReadMilliVolts(pin);
    delay(5);
  }
  return sum / (float)samples;
}

// Coefficients can each be plausible and still be nonsense together. An NTC's
// resistance falls as temperature rises, so check the curve does that across
// the deployment range. Same check as sensor-ntc.
bool shCoefficientsSane(float a, float b, float c) {
  const float probes[3] = { 5000.0f, 20000.0f, 80000.0f };
  float prev = 999.0f;
  for (int i = 0; i < 3; i++) {
    float lnR = logf(probes[i]);
    float denom = a + b * lnR + c * lnR * lnR * lnR;
    if (denom <= 0.0f) return false;
    float t = 1.0f / denom - 273.15f;
    if (t < -60.0f || t > 100.0f) return false;
    if (t >= prev) return false;
    prev = t;
  }
  return true;
}

float readNtc() {
  pinMode(NTC_EN_PIN, OUTPUT);
  digitalWrite(NTC_EN_PIN, LOW);
  // 100 nF against at most ~10k (R_series || R_ntc): RC <= 1 ms. 60 ms is ample.
  delay(60);

  analogRead(NTC_ADC_PIN);
  analogSetPinAttenuation(NTC_ADC_PIN, ADC_11db);
  analogRead(NTC_ADC_PIN);
  float mv = averageMv(NTC_ADC_PIN, NTC_SAMPLES);

  pinMode(NTC_EN_PIN, INPUT);

  float v = mv / 1000.0f;
  if (v <= 0.01f || v >= NTC_VCC - 0.01f) {
    Serial.printf("[NTC] %.0f mV — probe open or shorted\n", mv);
    return TEMP_ERROR;
  }

  const Settings& s = settings();
  float r   = s.rSeries * (NTC_VCC - v) / v;   // NTC on the high side
  float lnR = logf(r);
  float t   = 1.0f / (s.shA + s.shB * lnR + s.shC * lnR * lnR * lnR) - 273.15f;
  Serial.printf("[NTC] adc=%.0f mV  R=%.0f ohm  T=%.2f C\n", mv, r, t);

  if (t < -55.0f || t > 125.0f) return TEMP_ERROR;
  return t;
}

float readBatteryV() {
  pinMode(BAT_DIV_EN_PIN, OUTPUT);
  digitalWrite(BAT_DIV_EN_PIN, LOW);
  delay(10);   // 10 nF against 50k: RC 0.5 ms

  analogRead(BAT_ADC_PIN);
  analogSetPinAttenuation(BAT_ADC_PIN, ADC_11db);
  analogRead(BAT_ADC_PIN);
  float mv = averageMv(BAT_ADC_PIN, 20);

  pinMode(BAT_DIV_EN_PIN, INPUT);
  return mv / 1000.0f * BAT_DIVIDER_RATIO;
}

// Resting Li-ion curve. While charging the terminal voltage reads high, so the
// percentage is optimistic on mains — it is a backup gauge, not a fuel gauge.
static const struct { float v; uint8_t pct; } LIION[] = {
  {4.20f, 100}, {4.10f, 90}, {4.00f, 80}, {3.90f, 65}, {3.80f, 50},
  {3.75f,  40}, {3.70f, 30}, {3.65f, 20}, {3.60f, 12}, {3.50f,  5},
  {3.40f,   2}, {3.30f,  0},
};

uint8_t batteryPct(float v) {
  if (v < BAT_ERROR_V) return 255;
  const int n = sizeof(LIION) / sizeof(LIION[0]);
  if (v >= LIION[0].v)     return 100;
  if (v <= LIION[n - 1].v) return 0;
  for (int i = 0; i < n - 1; i++) {
    if (v <= LIION[i].v && v > LIION[i + 1].v) {
      float f = (v - LIION[i + 1].v) / (LIION[i].v - LIION[i + 1].v);
      return LIION[i + 1].pct + (uint8_t)(f * (LIION[i].pct - LIION[i + 1].pct));
    }
  }
  return 0;
}

Reading takeReading() {
  Reading r;
  r.onMains  = mainsPresent();
  r.charging = r.onMains && isCharging();
  r.batV     = readBatteryV();
  r.batPct   = batteryPct(r.batV);
  r.temp     = readNtc();
  Serial.printf("[READ] T=%.2f  bat=%.3f V (%u%%)  %s%s\n", r.temp, r.batV, r.batPct,
                r.onMains ? "mains" : "battery", r.charging ? ", charging" : "");
  return r;
}
